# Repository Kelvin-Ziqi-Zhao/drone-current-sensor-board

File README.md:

# Drone Current Sensor Board
High current sensor board for battery+capacitor power supply system.
[Lastest releases](https://github.com/Kelvin-Ziqi-Zhao/drone-current-sensor-board/releases/latest)
## Components and Design
- Use **RP2040** as MCU, **INA226** as power monitor chip.
- By using **0402** components, the size of module can be greatly reduced
## More Info
- DEBUG, UART test points and IIC select are reserved, which could help us during development
- This is the theory verification PCBA module of my follow-up power system, stay tuned...
>The hardware isn't been tested, please **CHECK THE CIRCUIT** before power-on

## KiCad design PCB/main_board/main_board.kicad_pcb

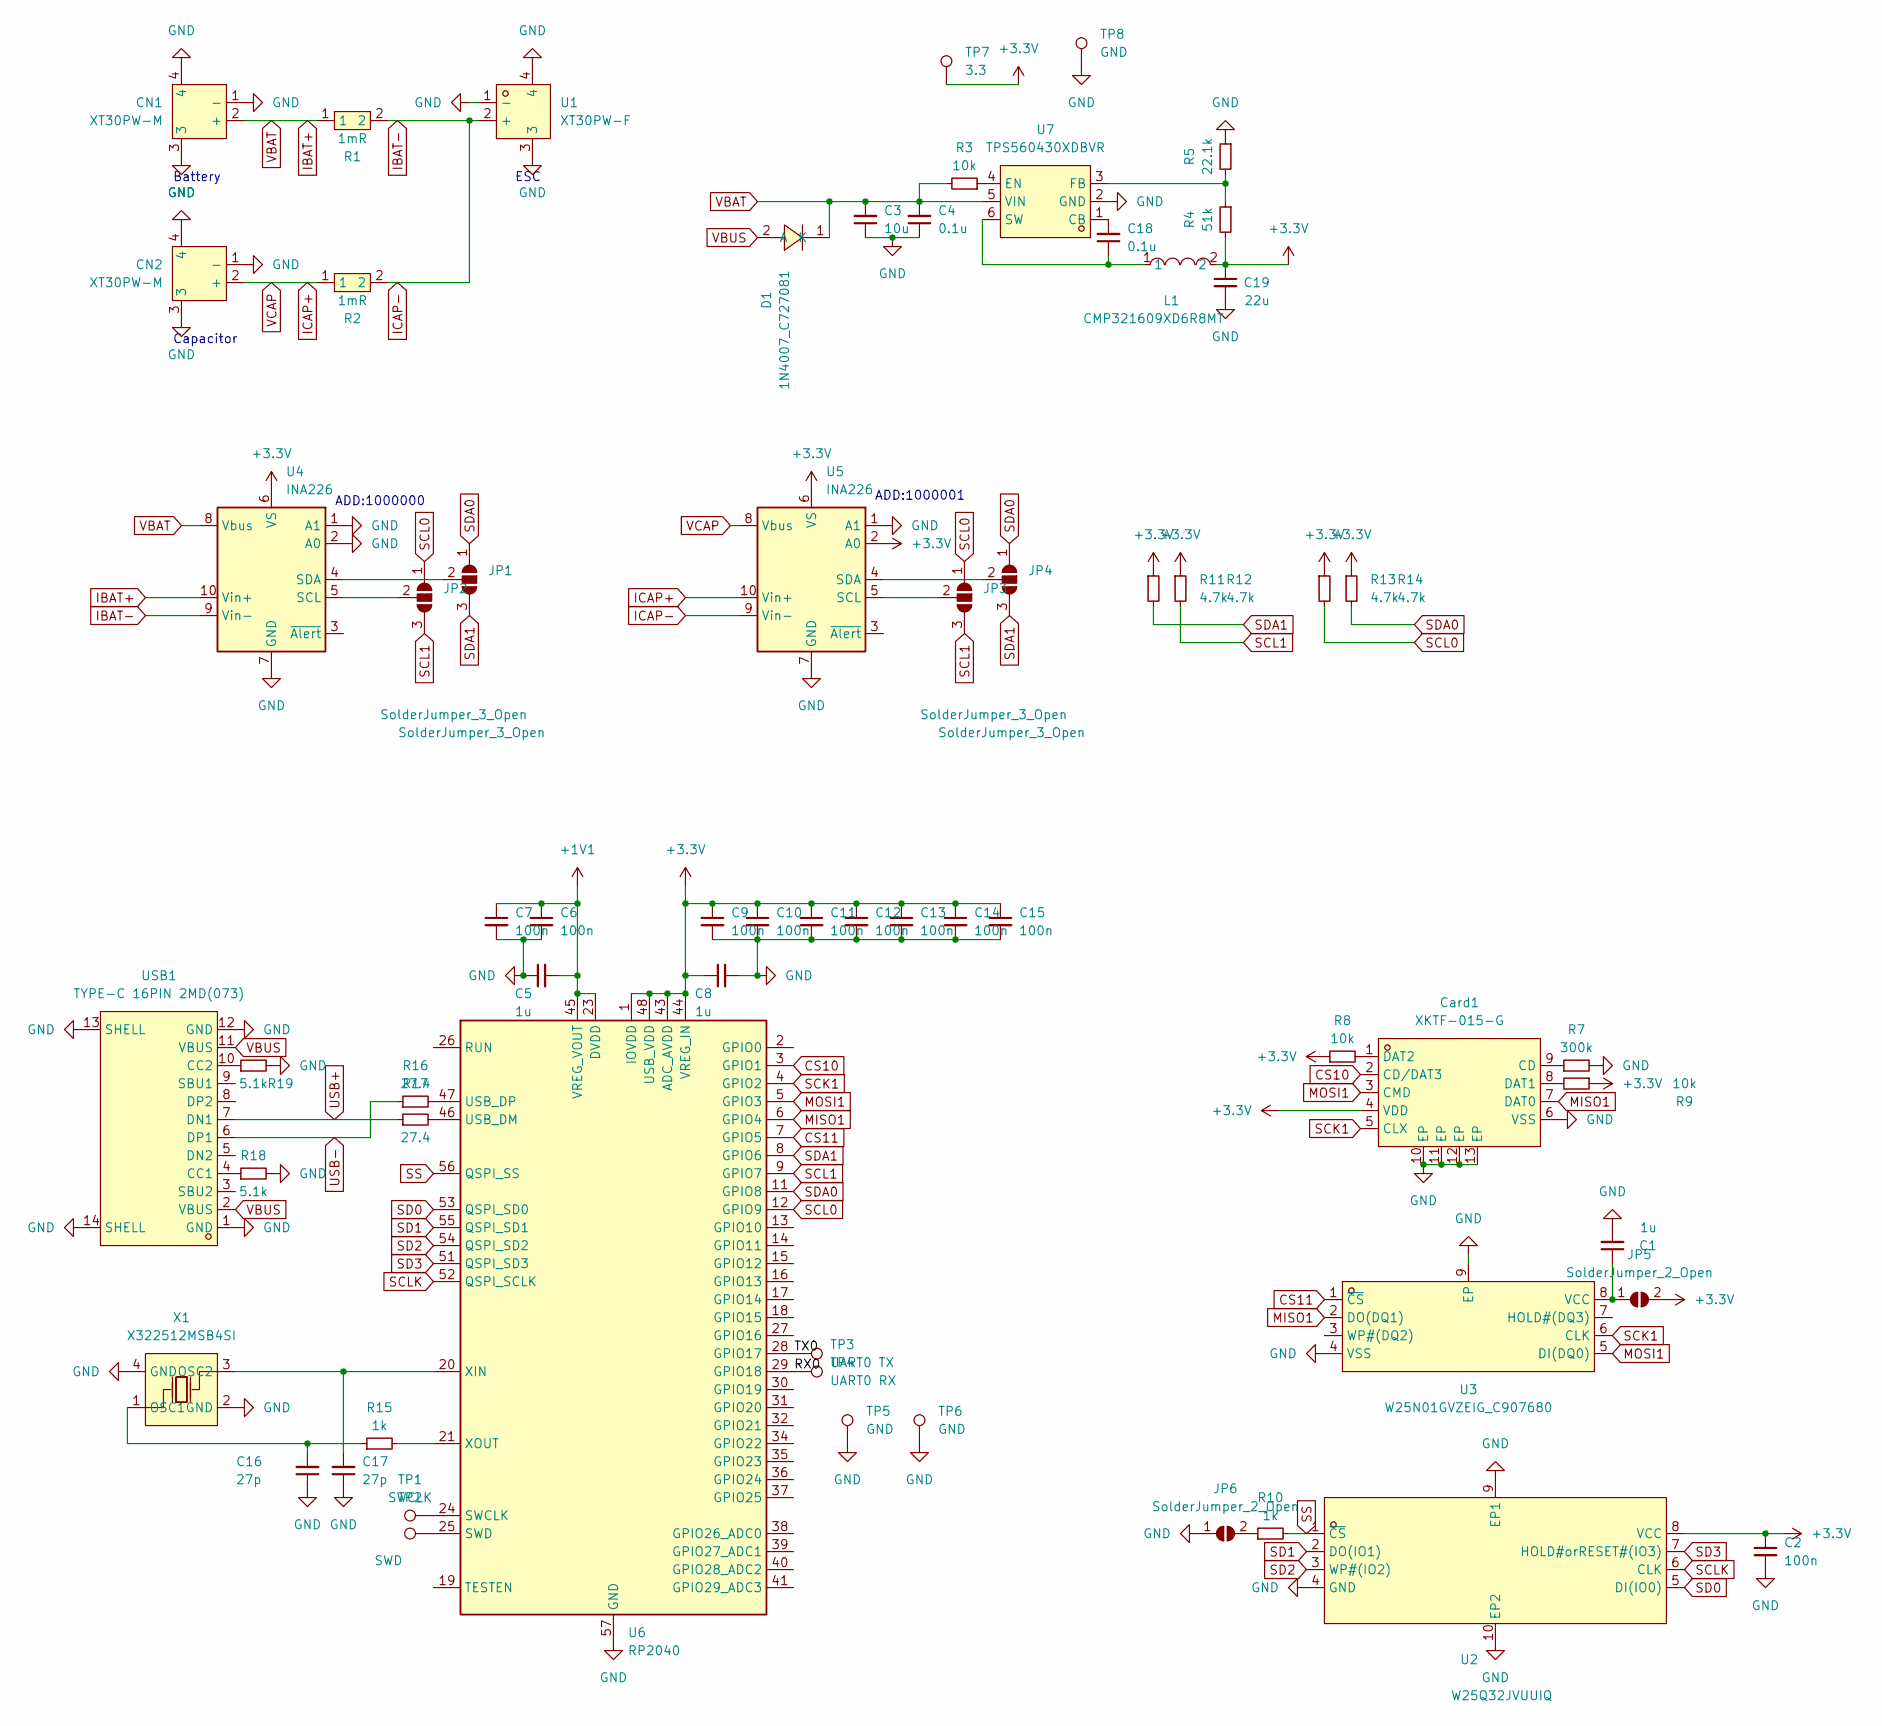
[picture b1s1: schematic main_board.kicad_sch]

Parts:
C1, C5, C8: 1u; C_0402_1005Metric
C2, C6, C7, C9, C10, C11, C12, C13, C14, C15: 100n; C_0402_1005Metric
C3: 10u; C_0603_1608Metric
C4: 0.1u; C_0603_1608Metric
C16, C17: 27p; C_0402_1005Metric
C18: 0.1u; C_0402_1005Metric
C19: 22u; C_0805_2012Metric
CN1, CN2: XT30PW-M; CONN-TH_XT30PW-M; LCSC Part C431092
Card1: XKTF-015-G; TF-SMD_XKTF-015-N; LCSC Part C1121874
D1: 1N4007_C727081; SMA_L4.3-W2.5-LS5.0-RD; LCSC Part C727081
JP1, JP2, JP3, JP4: SolderJumper_3_Open; SolderJumper-3_P1.3mm_Open_Pad1.0x1.5mm
JP5, JP6: SolderJumper_2_Open; SolderJumper-2_P1.3mm_Open_Pad1.0x1.5mm
L1: CMP321609XD6R8MT; L1206; LCSC Part C395031
R1, R2: 1mR; R3920; LCSC Part C5224161
R3: 10k; C_0402_1005Metric
R4: 51k; C_0402_1005Metric
R5: 22.1k; C_0402_1005Metric
R7: 300k; R_0402_1005Metric
R8, R9: 10k; R_0402_1005Metric
R10, R15: 1k; R_0402_1005Metric
R11, R12, R13, R14: 4.7k; R_0402_1005Metric
R16, R17: 27.4; R_0402_1005Metric
R18, R19: 5.1k; R_0402_1005Metric
TP1: SWCLK; TestPoint_Pad_1.5x1.5mm
TP2: SWD; TestPoint_Pad_1.5x1.5mm
TP3: UART0 TX; TestPoint_Pad_1.5x1.5mm
TP4: UART0 RX; TestPoint_Pad_1.5x1.5mm
TP5, TP6, TP8: GND; TestPoint_Pad_1.5x1.5mm
TP7: 3.3; TestPoint_Pad_1.5x1.5mm
U1: XT30PW-F; CONN-TH_XT30PW-F-1; LCSC Part C2913282
U2: W25Q32JVUUIQ; USON-8_L4.0-W3.0-P0.80-BL_WINBOND_UU; LCSC Part C2999380
U3: W25N01GVZEIG_C907680; WSON-8_L8.0-W6.10-P1.27-BL-EP; LCSC Part C907680
U4, U5: INA226; MSOP-10_L3.0-W3.0-P0.50-LS5.0-BL
U6: RP2040; QFN-56-1EP_7x7mm_P0.4mm_EP3.2x3.2mm
U7: TPS560430XDBVR; SOT-23-6_L2.9-W1.6-P0.95-LS2.8-BL; LCSC Part C524782
USB1: TYPE-C 16PIN 2MD(073); USB-C-SMD_TYPE-C-6PIN-2MD-073; LCSC Part C2765186
X1: X322512MSB4SI; OSC-SMD_4P-L3.2-W2.5-BL; LCSC Part C9002

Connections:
+1V1: C5.2, C6.1, C7.1, U6.23 (DVDD), U6.45 (VREG_VOUT), U6.50 (DVDD)
/RX0: TP4.1, U6.29 (GPIO18)
/TX0: TP3.1, U6.28 (GPIO17)
CS10: Card1.2 (CD/DAT3), U6.3 (GPIO1)
CS11: U3.1 (~CS), U6.7 (GPIO5)
IBAT-: R1.2, R2.2, U1.2 (+), U4.9 (Vin-), U5.9 (Vin-)
ICAP+: CN2.2 (+), R2.1, U5.8 (Vbus), U5.10 (Vin+)
MISO1: Card1.7 (DAT0), U3.2 (DO(DQ1)), U6.6 (GPIO4)
MOSI1: Card1.3 (CMD), U3.5 (DI(DQ0)), U6.5 (GPIO3)
unnamed: Card1.9 (CD), R7.1
unnamed: Card1.8 (DAT1), R9.2
unnamed: Card1.1 (DAT2), R8.2
unnamed: JP1.2 (C), U4.4 (SDA)
unnamed: JP2.2 (C), U4.5 (SCL)
unnamed: JP3.2 (C), U5.5 (SCL)
unnamed: JP4.2 (C), U5.4 (SDA)
unnamed: C1.1, JP5.1 (A), U3.8 (VCC)
unnamed: JP6.2 (B), R10.1
unnamed: TP1.1, U6.24 (SWCLK)
unnamed: TP2.1, U6.25 (SWD)
unnamed: R17.2, U6.46 (USB_DM)
unnamed: R16.2, U6.47 (USB_DP)
unnamed: C17.2, U6.20 (XIN), X1.3 (OSC2)
unnamed: R15.2, U6.21 (XOUT)
unnamed: C18.2, U7.1 (CB)
unnamed: R3.1, U7.4 (EN)
unnamed: R4.1, R5.2, U7.3 (FB)
unnamed: C18.1, L1.1, U7.6 (SW)
unnamed: R18.1, USB1.4 (CC1)
unnamed: R19.1, USB1.10 (CC2)
unnamed: C16.2, R15.1, X1.1 (OSC1)
SCK1: Card1.5 (CLX), U3.6 (CLK), U6.4 (GPIO2)
SCL0: JP2.1 (A), JP3.1 (A), R13.2, U6.12 (GPIO9)
SCL1: JP2.3 (B), JP3.3 (B), R12.2, U6.9 (GPIO7)
SCLK: U2.6 (CLK), U6.52 (QSPI_SCLK)
SD0: U2.5 (DI(IO0)), U6.53 (QSPI_SD0)
SD1: U2.2 (DO(IO1)), U6.55 (QSPI_SD1)
SD2: U2.3 (WP#(IO2)), U6.54 (QSPI_SD2)
SD3: U2.7 (HOLD#orRESET#(IO3)), U6.51 (QSPI_SD3)
SDA0: JP1.1 (A), JP4.1 (A), R14.2, U6.11 (GPIO8)
SDA1: JP1.3 (B), JP4.3 (B), R11.2, U6.8 (GPIO6)
SS: R10.2, U2.1 (~CS), U6.56 (QSPI_SS)
USB+: R17.1, USB1.7 (DN1)
USB-: R16.1, USB1.6 (DP1)
VBUS: D1.2 (A), USB1.2 (VBUS), USB1.11 (VBUS)

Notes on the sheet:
ADD:1000001
ESC
ADD:1000000
Battery
Capacitor

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
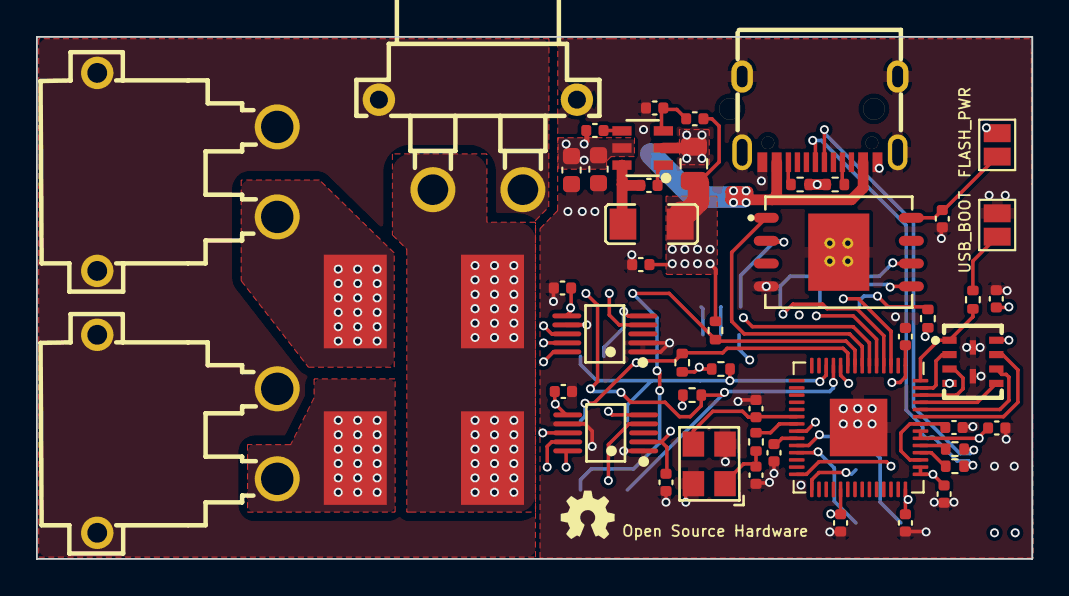
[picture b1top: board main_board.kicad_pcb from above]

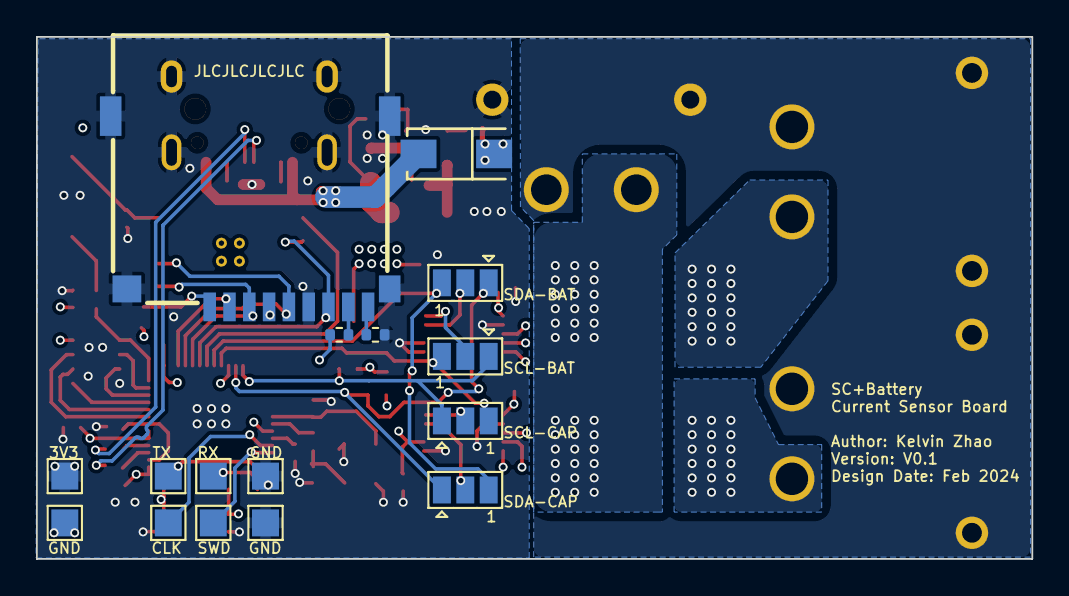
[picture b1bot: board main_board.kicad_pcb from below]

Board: 4 copper layers, 55.3 x 29.0 mm, 65 parts (16 on the bottom side), 48 nets.

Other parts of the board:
C4#2: 0.1u; C_0603_1608Metric

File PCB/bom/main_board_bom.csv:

"Id";"Designator";"Footprint";"Quantity";"Designation";"Supplier and ref";
1;"R2,R1";"R3920";2;"1mR";;;
2;"R19,R18";"R_0402_1005Metric";2;"5.1k";;;
3;"C9,C15,C7,C2,C12,C6,C10,C11,C14,C13";"C_0402_1005Metric";10;"100n";;;
4;"C4";"C_0402_1005Metric";1;"22u";;;
5;"U6";"QFN-56-1EP_7x7mm_P0.4mm_EP3.2x3.2mm";1;"RP2040";;;
6;"U4,U5";"VSSOP-10_3x3mm_P0.5mm";2;"INA226";;;
7;"C1,C8";"C_0402_1005Metric";2;"1u";;;
8;"X1";"OSC-SMD_4P-L3.2-W2.5-BL";1;"X322512MSB4SI";;;
9;"R15,R10";"R_0402_1005Metric";2;"1k";;;
10;"R8,R9";"R_0402_1005Metric";2;"10k";;;
11;"D1";"SMA_L4.3-W2.5-LS5.0-RD";1;"1N4007_C727081";;;
12;"USB1";"USB-C-SMD_TYPE-C-6PIN-2MD-073";1;"TYPE-C 16PIN 2MD(073)";;;
13;"CN1,CN2";"CONN-TH_XT30PW-M";2;"XT30PW-M";;;
14;"C3";"C_0402_1005Metric";1;"10u";;;
15;"C17,C16";"C_0402_1005Metric";2;"27p";;;
16;"R17,R16";"R_0402_1005Metric";2;"27.4";;;
17;"JP5,JP6";"SolderJumper-2_P1.3mm_Open_Pad1.0x1.5mm";2;"SolderJumper_2_Open";;;
18;"R11,R14,R12,R13";"R_0402_1005Metric";4;"4.7k";;;
19;"U1";"CONN-TH_XT30PW-F-1";1;"XT30PW-F";;;
20;"U3";"WSON-8_L8.0-W6.10-P1.27-BL-EP";1;"W25N01GVZEIG_C907680";;;
21;"U7";"SOT-89-3";1;"AZ1117-3.3";;;
22;"U2";"USON-8_L4.0-W3.0-P0.80-BL_WINBOND_UU";1;"W25Q32JVUUIQ";;;
23;"TP1";"TestPoint_Pad_1.5x1.5mm";1;"SWCLK";;;
24;"TP3";"TestPoint_Pad_1.5x1.5mm";1;"UART0 TX";;;
25;"JP3,JP4,JP2,JP1";"SolderJumper-3_P1.3mm_Open_Pad1.0x1.5mm";4;"SolderJumper_3_Open";;;
26;"Card1";"TF-SMD_XKTF-015-N";1;"XKTF-015-G";;;
27;"TP5,TP6";"TestPoint_Pad_1.5x1.5mm";2;"GND";;;
28;"TP2";"TestPoint_Pad_1.5x1.5mm";1;"SWD";;;
29;"TP4";"TestPoint_Pad_1.5x1.5mm";1;"UART0 RX";;;
30;"R7";"R_0402_1005Metric";1;"300k";;;

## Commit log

2024-02-12 Rename .ignore to .gitignore
2024-02-12 Local file update
2024-02-12 Create pcb layout
2024-02-12 Fundamental pcb layout
2024-02-12 Change INA226 connection
2024-02-12 add PCB outline, redesign power component
2024-02-12 basic layout complete
2024-02-12 stage pull
2024-02-12 project_lib push
2024-02-13 Change lib to relative path
2024-02-14 Add W25Q32 chip to local lib
2024-02-14 Update W25 uson
2024-02-14 Add EEPROM to mcu; Change R and C to 0402
2024-02-14 Add image
2024-02-14 Fundamental layout complete
2024-02-14 Change IIC0, IIC1 and SPI connection GPIO
2024-02-14 Complete SPI Flash and part of decouple capacitor layout
2024-02-14 Complete INA226 IIC trace
2024-02-14 Complete high current trace
2024-02-14 Complete VBUS trace; Adjust Flash position
2024-02-14 Update image
2024-02-16 Complete USB DP routing
2024-02-16 PCB route complete
2024-02-16 Optimize ref to DCR
2024-02-16 DRC Check complete
2024-02-16 Place text for test point; Disconnect a ground error connection
2024-02-16 Thicker the single ground connection
2024-02-16 Ready to JLC
2024-02-16 Renew Picture
2024-02-17 Change LDO to BUCK converter
2024-02-17 Ready for JLC for second time
2024-02-17 Export for JLC
2024-02-17 Remove extra current carrier
2024-02-17 Add Custom ID
2024-02-17 Change vias drills to 0.3/0.5mm
2024-02-18 Change INA226 package for SMT
2024-02-26 Add latest release
2024-02-28 import from https://github.com/elschopi/TI_INA226_micropython
2024-02-28 change release tag to v0.1.0
2024-02-28 successfully access ina226 though iic bus
2024-02-29 Successfully access two INA226 in one bus
2024-02-29 change dir
2024-03-02 Build up a loop receiver
2024-03-02 Successfully access sd card and write text file
2024-03-02 change spi_access.py dir
2024-03-04 import rpi-pico-ssd1306
2024-03-04 change oled dir
2024-03-05 update demo program
2024-03-14 sd test
2024-03-14 oled display hz
2024-03-15 Change INA226 module sampling average number
2024-03-22 read to test
2024-03-22 2nd system program
